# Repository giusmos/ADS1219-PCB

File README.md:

# ADS1219-PCB
 PCB schematic and layout for 24bit ADC 1219 from TI

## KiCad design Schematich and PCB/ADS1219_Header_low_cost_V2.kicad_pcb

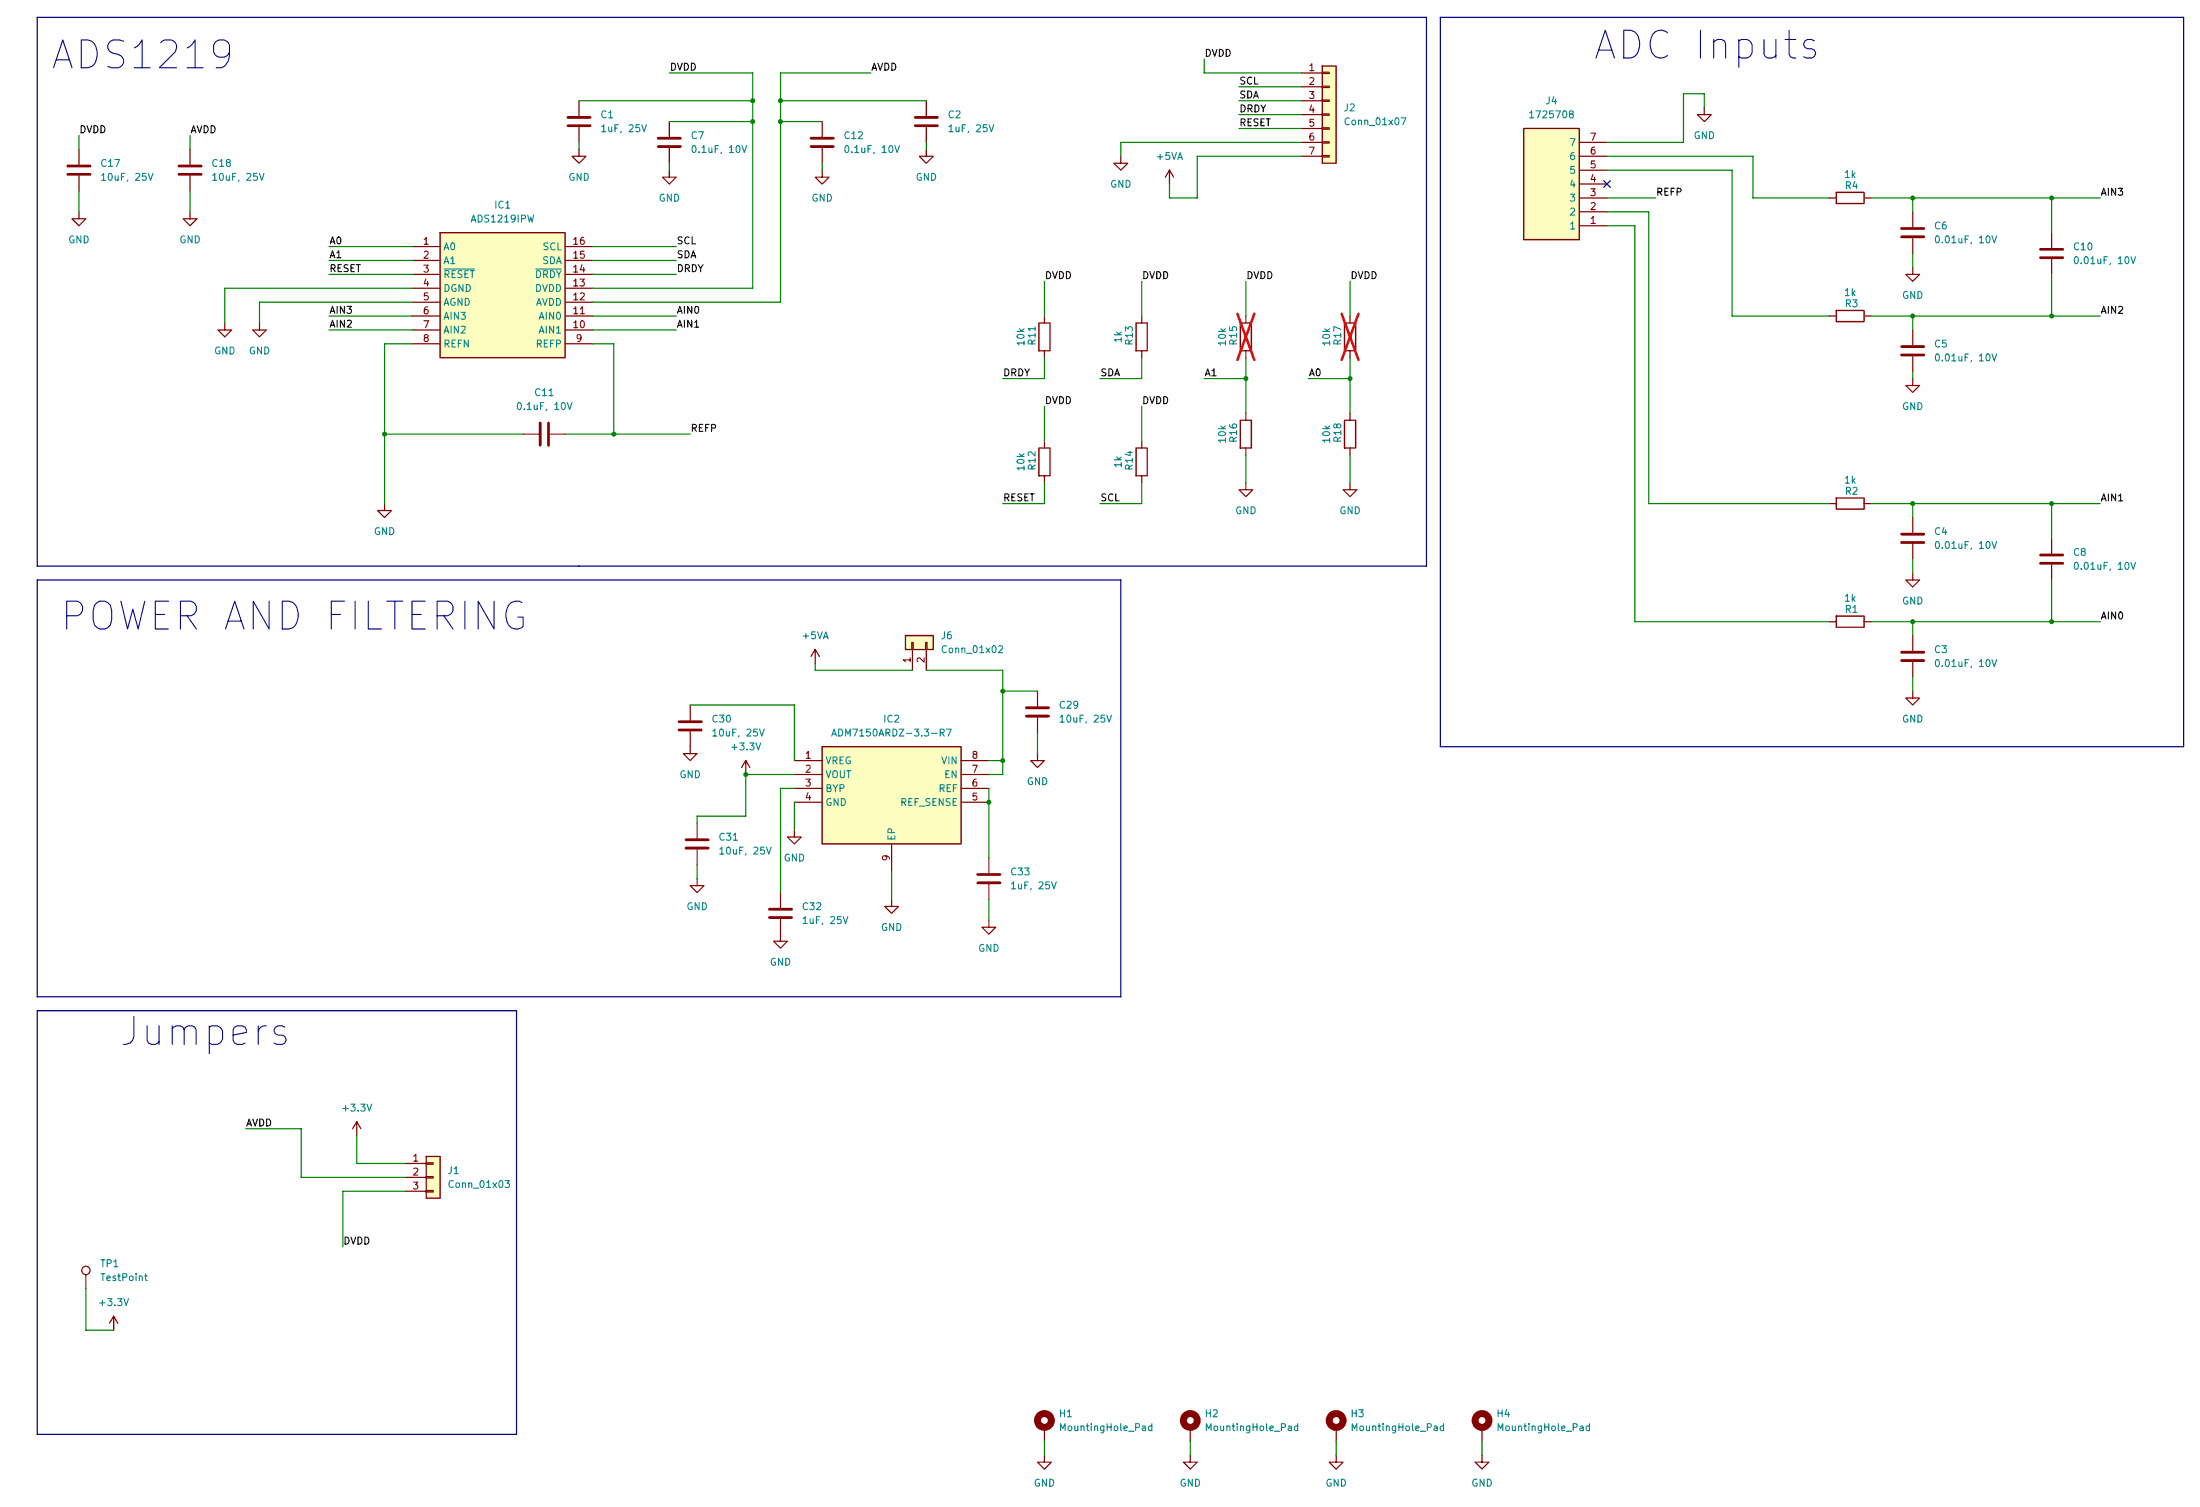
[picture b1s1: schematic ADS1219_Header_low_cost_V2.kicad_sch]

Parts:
C1, C2, C32, C33: 1uF, 25V; C_0603_1608Metric_Pad1.08x0.95mm_HandSolder
C3, C4, C5, C6, C8, C10: 0.01uF, 10V; C_0603_1608Metric_Pad1.08x0.95mm_HandSolder
C7, C11, C12: 0.1uF, 10V; C_0805_2012Metric_Pad1.18x1.45mm_HandSolder
C17, C18, C29, C30, C31: 10uF, 25V; C_0805_2012Metric_Pad1.18x1.45mm_HandSolder
H1, H2, H3, H4: MountingHole_Pad; MountingHole_2.2mm_M2_Pad_Via
IC1: ADS1219IPW; SOP65P640X120-16N; Mouser Part Number 595-ADS1219IPW
IC2: ADM7150ARDZ-3.3-R7; SOIC127P600X175-9N; Mouser Part Number 584-ADM7150ARDZ3.3R7
J1: Conn_01x03; PinHeader_1x03_P2.54mm_Vertical
J2: Conn_01x07; PinHeader_1x07_P2.54mm_Vertical
J4: 1725708; Mouser Part Number 651-1725708
J6: Conn_01x02; PinHeader_1x02_P2.54mm_Vertical
R1, R2, R3, R4, R13, R14: 1k; R_0805_2012Metric_Pad1.20x1.40mm_HandSolder
R11, R12, R16, R18: 10k; R_0805_2012Metric_Pad1.20x1.40mm_HandSolder
R15, R17: 10k; R_0805_2012Metric_Pad1.20x1.40mm_HandSolder; not fitted
TP1: TestPoint; TestPoint_Pad_D1.0mm

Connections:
+3.3V: C31.1, IC2.2 (VOUT), J1.1, TP1.1
+5VA: J2.7, J6.1
/A0: IC1.1 (A0), R17.2, R18.1
/A1: IC1.2 (A1), R15.2, R16.1
/AIN0: C3.1, C8.2, IC1.11 (AIN0), R1.1
/AIN1: C4.1, C8.1, IC1.10 (AIN1), R2.1
/AIN2: C5.1, C10.2, IC1.7 (AIN2), R3.1
/AIN3: C6.1, C10.1, IC1.6 (AIN3), R4.1
/AVDD: C2.1, C12.1, C18.1, IC1.12 (AVDD), J1.2
/DRDY: IC1.14 (~DRDY), J2.4, R11.2
/DVDD: C1.1, C7.1, C17.1, IC1.13 (DVDD), J1.3, J2.1, R11.1, R12.1, R13.1, R14.1, R15.1, R17.1
/REFP: C11.1, IC1.9 (REFP), J4.3
/RESET: IC1.3 (~RESET), J2.5, R12.2
/SCL: IC1.16 (SCL), J2.2, R14.2
/SDA: IC1.15 (SDA), J2.3, R13.2
GND: C1.2, C2.2, C3.2, C4.2, C5.2, C6.2, C7.2, C11.2, C12.2, C17.2, C18.2, C29.2, C30.2, C31.2, C32.2, C33.2, H1.1, H2.1, H3.1, H4.1, IC1.4 (DGND), IC1.5 (AGND), IC1.8 (REFN), IC2.4 (GND), IC2.9 (EP), J2.6, J4.7, R16.2, R18.2
unnamed: C32.1, IC2.3 (BYP)
unnamed: C29.1, IC2.7 (EN), IC2.8 (VIN), J6.2
unnamed: C33.1, IC2.5 (REF_SENSE), IC2.6 (REF)
unnamed: C30.1, IC2.1 (VREG)
unnamed: J4.1, R1.2
unnamed: J4.2, R2.2
unnamed: J4.5, R3.2
unnamed: J4.6, R4.2

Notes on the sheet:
ADS1219
Jumpers
ADC Inputs
POWER AND FILTERING

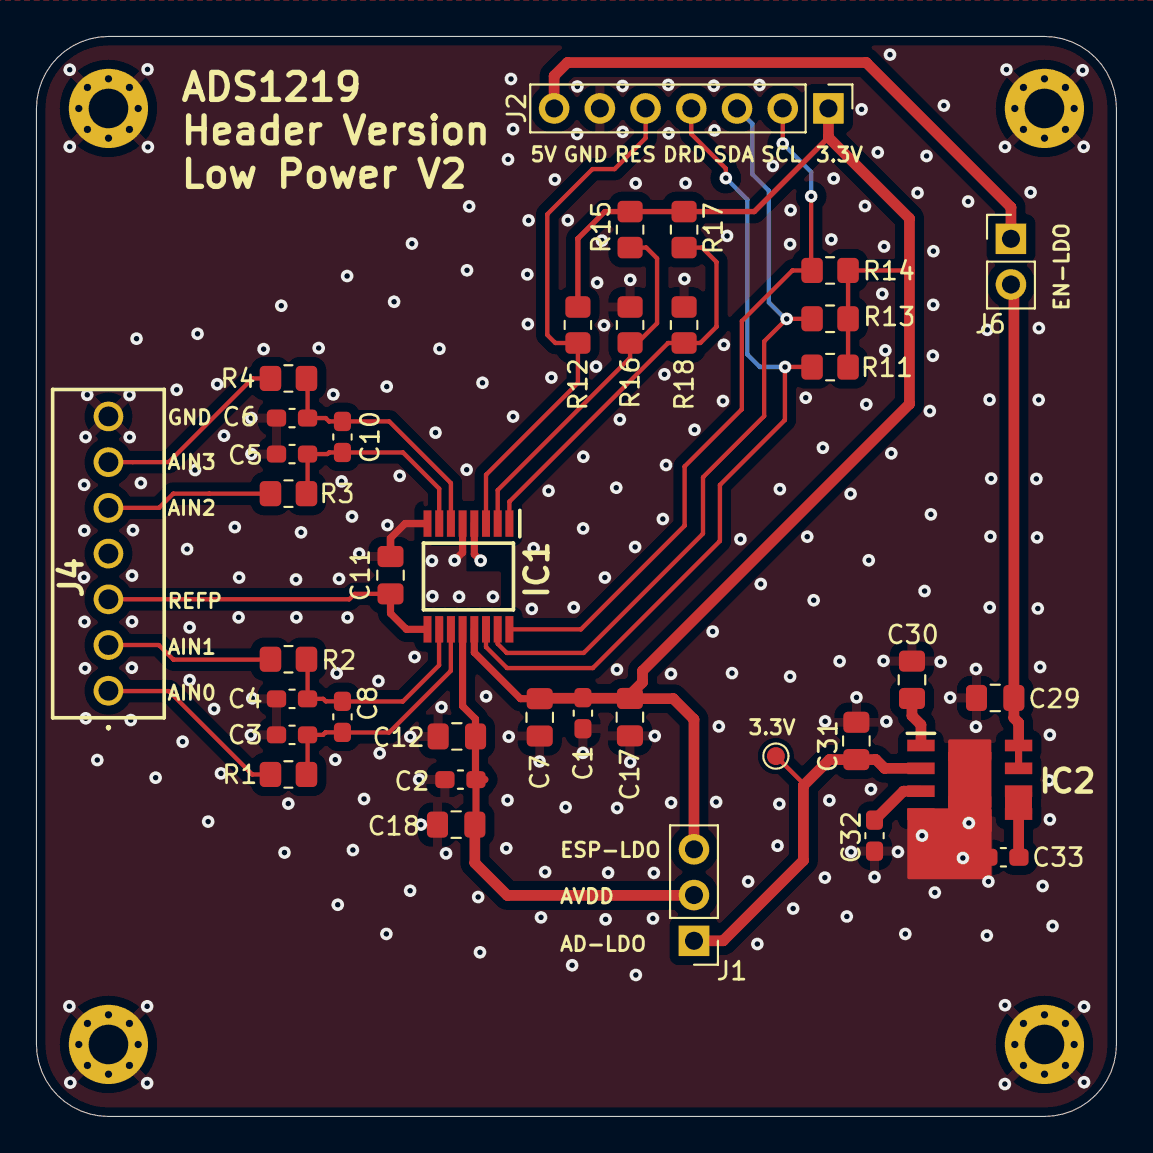
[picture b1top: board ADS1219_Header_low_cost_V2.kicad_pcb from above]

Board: 4 copper layers, 60.0 x 60.0 mm, 41 parts (0 on the bottom side), 24 nets.

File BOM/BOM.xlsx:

Item # | Designator | Quantity | Component | *Package/Footprint | Type
1 | C1,C2,C32,C33 | 4 | 1uF, 25V | _0603 | SMD
2 | C3,C4,C5,C6,C8,C10 | 6 | 0.01uF, 10V | _0603 | SMD
3 | C7,C11,C12 | 3 | 100nF, 10V | _0805 | SMD
4 | C17,C18,C29,C30,C31 | 5 | 10uF, 25V | _0805 | SMD
5 | IC1 | 1 | ADS1219IPWR | TSSOP-16 | SMD
6 | IC2 | 1 | ADM7150ARDZ-3.3-R7 |  | SMD
7 | R1,R2,R3,R4,R13,R14 | 6 | 1K | _0805 | SMD
8 | R11,R12,R16,R18 | 4 | 10K | _0805 | SMD
9 | R15,R17 | 0 | 10K | _0805 | SMD

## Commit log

2024-12-27 Added latest files
2024-12-27 removed step file
